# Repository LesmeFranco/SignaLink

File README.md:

<div align="center">

</div>

<div align="center">

# Tus gestos hablan, SignaLink traduce

</div>

## 🔗 Acceso a página web:

https://signalink2025.com

## 🗓️ Objetivo de Proyecto:

SignaLink tiene como objetivo principal traducir la lengua de señas para lograr la inclusión de personas sordas en el ámbito escolar.

## 🌎 Visión a futuro

Otro objetivo propuesto a largo plazo es seguir difundiendo esta idea en futuras generaciones para poder proveerles un mejor manejo en la vida cotidiana a este tipo de personas, permitiendole agilizar su vida social o simplemente la comunicación sin barerras con otras personas.

## 💭 ¿De dónde surgió la idea?

Esta idea surgió en una conversación con la bibliotecaria de nuestra escuela que nos dio a conocer cuan reservadas son estas personas en la sociedad y cuantos desafios deben afrontar a diario. A traves de todo esto planteamos posibles soluciones para facilitarle sus vidas inicialmente en las escuelas y asi empezo toda esta aventura.

## 🖐 Descripción del proyecto:

Nuestro proyecto esta principalmente equipado con sensores flex, giroscopos y acelerómetros que detectan los movimientos de los dedos.

Estos datos que arrojan los sensores son capturados por un ESP32 C3 Super Mini ubicado en la muñeca y enviados a un Computer module 4 (CM4) a traves de un sistema de mensajeria (MQTT) ubicado en el pecho/cintura. Esta CM4 integra una Inteligencia Artificial (IA) que se encarga de procesar estos datos recibidos para descubrir que gesto se intentó hacer. Una vez realizado este proceso se convertira mediante PIPER-TTS a formato audio reproducible por un parlante, permitiendo así que las personas que se comunican mediante la lengua de señas puedan expresar su mensaje de forma audible para que cualquier receptor lo comprenda.

En paralelo, un micrófono direccional se encargará de captar la voz de la persona que quiera comunicarse, esas palabras serán procesadas por la CM4 utilizando un modelo de reconocimiento de voz (Vosk -> Offline) y en forma de texto se mostrará finalmente a través de un LCD OLED (SSD1306)

<div align="center">

</div>

## 🛠️ Componentes a utilizar:

| Componentes                     | Links                                                                                                                                                                                                                                                                                                                                                                                                                                                                                                                                                                                                                                                                                                                                                                                            |
| ------------------------------- | ------------------------------------------------------------------------------------------------------------------------------------------------------------------------------------------------------------------------------------------------------------------------------------------------------------------------------------------------------------------------------------------------------------------------------------------------------------------------------------------------------------------------------------------------------------------------------------------------------------------------------------------------------------------------------------------------------------------------------------------------------------------------------------------------ |
| Raspberry Pi Compute Module 4   | [Raspberry Pi Compute Module 4 - ELEMON](https://www.elemon.com.ar/products/detail/code/AR681RA642)                                                                                                                                                                                                                                                                                                                                                                                                                                                                                                                                                                                                                                                                                              |
| ESP32-C3 Super Mini             | [ESP32-C3 Super Mini - Mercado Libre](https://articulo.mercadolibre.com.ar/MLA-1933180704-placa-desarrollo-esp32-c3-super-mini-wifi-bluetooth-sgk-_JM#polycard_client=search-nordic&position=18&search_layout=grid&type=item&tracking_id=a6179d80-9c2f-448f-931d-3f6b0744610e&wid=MLA1933180704&sid=search)                                                                                                                                                                                                                                                                                                                                                                                                                                                                                      |
| Sensores Flex                   | [Sensores Flex - Mercado Libre](https://articulo.mercadolibre.com.ar/MLA-621168012-flex-sensor-45-o-degrees-10-30-kohms-sensor-reflectivo-_JM#polycard_client=search-nordic&position=22&search_layout=stack&type=item&tracking_id=d09a116e-7fa9-4e61-b811-829b67d77fb1&wid=MLA621168012&sid=search)                                                                                                                                                                                                                                                                                                                                                                                                                                                                                              |
| Parlante                        | [ Mini Parlante- Mercado Libre](https://articulo.mercadolibre.com.ar/MLA-926965993-mini-parlante-mylar-50mm-8-ohms-05w-audio-arduino-nubbeo-_JM#polycard_client=search-nordic&position=8&search_layout=stack&type=item&tracking_id=5afdc171-789b-4858-9908-6e8644b818c2&wid=MLA926965993&sid=search)                                                                                                                                                                                                                                                                                                                                                                                                                                                                                             |
| Modulo Amplificador             | [ PAM8403 - Mercado Libre](https://www.mercadolibre.com.ar/mini-amplificador-digital-pam8403-audio-estereo-3w-nubbeo/up/MLAU237136317?pdp_filters=item_id:MLA872767061&matt_tool=93069454&matt_internal_campaign_id=345755545&matt_word=&matt_source=google&matt_campaign_id=22943760643&matt_ad_group_id=187007705242&matt_match_type=&matt_network=g&matt_device=c&matt_creative=774178775740&matt_keyword=&matt_ad_position=&matt_ad_type=pla&matt_merchant_id=5381779497&matt_product_id=MLA872767061&matt_product_partition_id=2424609165763&matt_target_id=pla-2424609165763&cq_src=google_ads&cq_cmp=22943760643&cq_net=g&cq_plt=gp&cq_med=pla&gad_source=1&gad_campaignid=22943760643&gclid=CjwKCAjwx-zHBhBhEiwA7Kjq67psJOORAgfFyvkqrNDuf2QOjtHhOilyAz1d6FZmyiqMh8wAA7Ma8xoCBCEQAvD_BwE) |
| Micrófono                       | [ Corbatero Carello C11 - Mercado Libre](https://www.mercadolibre.com.ar/microfono-inalambrico-corbatero-lavalier-carrello-c11-adaptador-usb-c-a-lightning-estuche-de-carga-antena-usb-c-1x-microfono-color-negro/p/MLA44118282)                                                                                                                                                                                                                                                                                                                                                                                                                                                                                                                                                                 |
| Baterias                        | [ Lipo 3.7V - Mercado Libre](https://articulo.mercadolibre.com.ar/MLA-823943306-bateria-litio-polimero-lipo-37v-1200mah-drones-helicopteros-_JM#polycard_client=search-nordic&position=11&search_layout=stack&type=item&tracking_id=00997a8f-a302-41cd-929e-7f9b96588b73&wid=MLA823943306&sid=search)                                                                                                                                                                                                                                                                                                                                                                                                                                                                                            |
| Sensor Giroscopo y Acelerometro | [MPU6050 - Mercado Libre](https://articulo.mercadolibre.com.ar/MLA-1464073846-acelerometro-giroscopo-mpu6050-6-ejes-gy-521-pic-arduino-_JM#polycard_client=search-nordic&position=4&search_layout=grid&type=item&tracking_id=1592b6fb-67c2-4128-a466-704776d0e915&wid=MLA1464073846&sid=search)                                                                                                                                                                                                                                                                                                                                                                                                                                                                                                  |
| Step Up 5V                      | [ MT3608 - Mercado Libre](https://articulo.mercadolibre.com.ar/MLA-1410408453-5-fuente-mt3608-step-up-buck-boost-elevador-dc-dc-28v-2a-_JM#polycard_client=search-nordic&backend_model=search-backend&position=20&search_layout=stack&type=item&tracking_id=d4915a5c-d355-42a4-b246-3798a3844913&wid=MLA1410408453&sid=search)                                                                                                                                                                                                                                                                                                                                                                                                                                                                   |
| LCD OLED                        | [LCD SSD1306 - Mercado Libre](https://articulo.mercadolibre.com.ar/MLA-1899526208-pantalla-display-oled-091-pulgadas-128x32-i2c-ssd1306-_JM)                                                                                                                                                                                                                                                                                                                                                                                                                                                                                                                                                                                                                                                     |

## 💻 Instalación y Uso

1. Clonar el repositorio:
   ```bash
   git clone https://github.com/impatrq/SignaLink
   ```
2. Entrar a la carpeta rpizero2W.
   ```bash
   cd SignaLink/rpizero2W
   ```
3. Darle permisos de ejecucion al script de instalación.
   ```bash
   chmod +x install.sh
   ```
4. Ejecutar el Script.
   ```bash
   ./install.sh
   ```
5. Comenzar su uso.

## 🧑🏽‍💻 Integrantes

| Integrantes           | Responsabilidades                     | Tareas Secundarias                 |
| --------------------- | ------------------------------------- | ---------------------------------- |
| Albornoz Thiago       | Gestión de Redes Sociales y Marketing | Desarrollo de Software             |
| Erbino Sebastián      | Diseño del Prototipo                  | Integración de hardware            |
| Franco Valentin       | Armado de Hardware                    | Instalación y conexión de hardware |
| Lesme Franco          | Armado de software                    | Diseño del prototipo               |
| Poggi Lorenzo         | Registro de Seguimiento               | Programación del sistema           |
| Sarniguette Valentino | Prueba electronica                    | Armado de circuitos                |

## 🤝 Colaboración:

Este es el comienzo de un prototipo realizado a base de nuestros conocimientos, si le gustaria formar parte de SignaLink, nos ayudaría su colaboración en:

- Perfeccionar el código.
- Mejorar la infraestructura tecnológica.
- Creación de manuales y realización de pruebas.
- Apoyo financiero para la investigación y el desarrollo.

## 📱 Contactanos:

 <div style="display: flex; justify-content: space-around;">

## 📱 Contactos personales

### 1. Albornoz Thiago

### 2. Erbino Sebastian

### 3. Franco Valentin

### 4. Lesme Franco

### 5. Poggi Lorenzo

</a>

### 6. Sarniguette Valentino

---

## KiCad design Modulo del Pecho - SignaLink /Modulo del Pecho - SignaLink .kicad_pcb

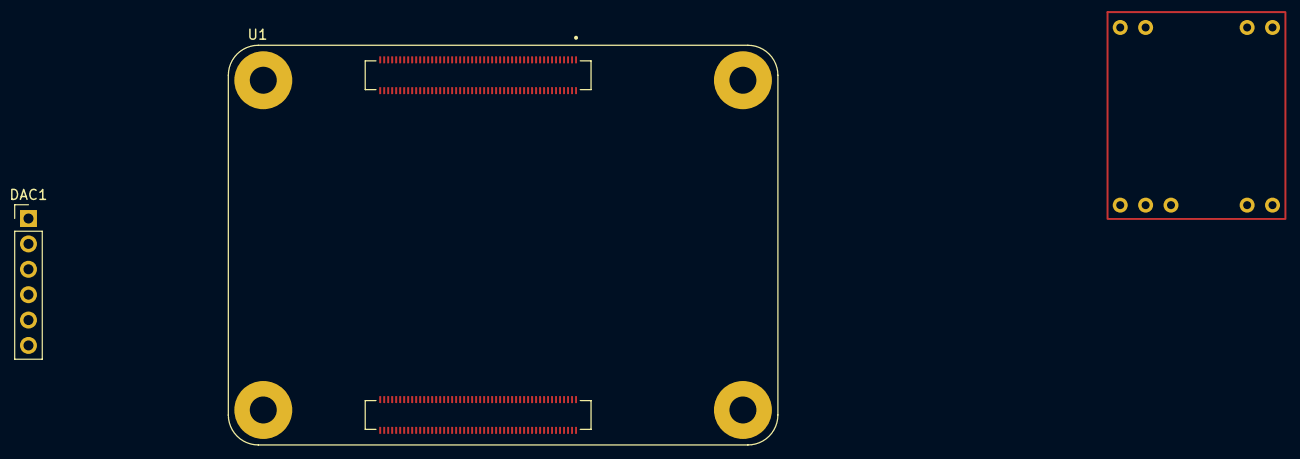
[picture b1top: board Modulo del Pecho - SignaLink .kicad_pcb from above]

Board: 2 copper layers, 3 parts (0 on the bottom side), 5 nets, no tracks yet.

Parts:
AMPL1: PAM8403
DAC1: PinHeader_1x06_P2.54mm_Vertical
U1: Raspberry; MODULE_SC0682

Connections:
unnamed: DAC1.1 (VIN), U1.77 (+5V(INPUT)), U1.79 (+5V(INPUT)), U1.81 (+5V(INPUT)), U1.83 (+5V(INPUT)), U1.85 (+5V(INPUT)), U1.87 (+5V(INPUT))
unnamed: U1.88 (CM4_1.8V(OUTPUT)), U1.90 (CM4_1.8V(OUTPUT))
unnamed: U1.84 (CM4_3.3V(OUTPUT)), U1.86 (CM4_3.3V(OUTPUT))
unnamed: U1.1 (GND), U1.2 (GND), U1.7 (GND), U1.8 (GND), U1.13 (GND), U1.14 (GND), U1.22 (GND), U1.23 (GND), U1.32 (GND), U1.33 (GND), U1.42 (GND), U1.43 (GND), U1.52 (GND), U1.53 (GND), U1.59 (GND), U1.60 (GND), U1.65 (GND), U1.66 (GND), U1.71 (GND), U1.74 (GND), U1.98 (GND), U1.107 (GND), U1.108 (GND), U1.113 (GND), U1.114 (GND), U1.119 (GND), U1.120 (GND), U1.125 (GND), U1.126 (GND), U1.131 (GND), U1.132 (GND), U1.137 (GND), U1.138 (GND), U1.144 (GND), U1.150 (GND), U1.155 (GND), U1.156 (GND), U1.161 (GND), U1.162 (GND), U1.167 (GND), U1.168 (GND), U1.173 (GND), U1.174 (GND), U1.179 (GND), U1.180 (GND), U1.185 (GND), U1.186 (GND), U1.191 (GND), U1.192 (GND), U1.197 (GND), U1.198 (GND)
unnamed: U1.SH1 (MOUNTING_PADS), U1.SH2 (MOUNTING_PADS), U1.SH3 (MOUNTING_PADS), U1.SH4 (MOUNTING_PADS)

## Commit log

2025-06-06 feat: agrego carpeta funcional de la confugracion BLE
2025-06-06 feat: agrego README
2025-06-06 chore: modificaciones en el codigo
2025-06-09 feat: agrego archiv .gitignore
2025-06-09 prueba flex
2025-06-10 chore: eliminación de carpetas
2025-06-10 chore: eliinacion de gitigonre
2025-06-10 feat: nuevo funcionamiento de la conexión BLE
2025-06-11 feat: borro elementos innecesarios
2025-06-11 flex
2025-06-11 fix: corregir errores en la funcionalidad BLE
2025-06-12 feat: agregar funcional BLE para sensores flex
2025-06-12 nueva rama BLE
2025-06-12 feat.BLE
2025-06-13 feat: actualizo archivos
2025-06-13 Directorio de raspberry Pi Zero 2W con Script de instalacion de dependencias necesarias
2025-06-19 Update README.md
    cambio en el LCD
2025-06-19 feat: Actualizo nuevas funciones, imagenes, y otras cosas para la página web
2025-06-19 chore: muevo de lugar los archivos
2025-06-19 chore: subo archivos borrados accidentalmente
2025-06-19 fix: corrección del readme
2025-06-25 UART
2025-07-10 Modificaciones y eliminacion de requerimientos innecesarios
2025-07-12 Modificaciones del requirements.txt
2025-07-12 Primera prueba del microfono y primero reconocimiento de voz realizado
2025-08-04 feat: actualizo imagenes del readme
2025-08-04 fix: imagenes
2025-08-20 muevo la v1.1 de la pagina a su carpeta correspondiente
2025-08-25 nuevos parametros de sensores flex
2025-08-26 chore: elimino carpeta que esta de mas
2025-08-26 feat: agregar funcion del oled lcd
2025-08-26 Revert "feat: agregar funcion del oled lcd"
2025-08-27 Muevo carpetas
2025-08-27 cambio dos valores de parametros de flex
2025-08-27 fix: modificaciones en gatt_client
2025-08-27 chore: elimino carpeta vieja de gatt_client
2025-08-27 feat: ahora si agrego la carpeta que esta bien
2025-09-02 fix: elimino vieja carpeta de pagina web
2025-09-02 feat: Acomodo todo en carpetas y subo version final de webpage
2025-09-02 chore: elimino licencia
2025-09-02 feat: Datasheets usados
2025-09-02 feat: Agrego datasheet de flex
2025-09-03 feat: nueva funcion ble
2025-09-03 agrego imagen
2025-09-03 cambio de recepcion en cliente de notificacion
2025-09-03 cambios de informacion enviada al cliente
2025-09-03 inicializando angulos
2025-09-03 chore: sdkconfig
2025-09-03 chore: .vscode
2025-09-03 docs: Muevo todo a carpetas correspondientes
2025-09-03 cambios en notificacion de client
2025-09-03 edit para que arranquen los flex desde la misma resistencia
2025-09-03 creo carpetas de experimentación e imagenes
2025-09-03 muevo carpeta del MAX9814 y fixeo readme
2025-09-03 agrego carpeta de img
2025-09-03 creo carpeta de imagenes y subo logo al readme
2025-09-03 fix en proceso
2025-09-03 Elimino carpeta rpizero2w para trabajar en otra rama
2025-09-09 fix: codigo corriendo
2025-09-16 docs: datasheet del PCM5102 agregado
2025-09-18 docs: datasheet de referencias
2025-09-19 preparo para PR
2025-09-19 docs: muevo carpetas a su respectivo lugar
2025-09-19 docs: creo carpeta principal de prototipo 3D
2025-09-19 docs: agrego anteproyecto
2025-09-26 clean: limpieza de archivos en la rama de placaas
2025-09-26 feat: agrego carpeta del modulo del pecho
    En esta carpeta se encuentra el esquematico y el pcb para la placa que vamos a hacer para el modulo del pecho
2025-09-26 feat: agrego carpeta que contiene las bibliotecas
    Esta carpeta contiene tanto los esquemas de los sensores y sus huellas
2025-09-26 feat: adjunto imagenes de las placas de la muñeca
2025-09-26 fix: modificaciones en el README
2025-09-26 refactor: arreglo tamaño de imagenes
2025-09-26 Primer opción para soporte de sensores flex
2025-09-26 Separaciones de las falanges
    Con el fin de que el soporte sea funcional, tuve que modificar el archivo en SolidWorks para su impresión
2025-09-26 Segunda opción para soporte de los sensores flex
    Pensando en la experiencia del usuario y el posible uso diario del dispositivo, decidimos cambiar el diseño por uno mucho más ergonómico y compacto
2025-09-26 Reescala del diseño del soporte
    El tamaño del diseño era incorrecto y no permitía el uso para los usuarios
2025-09-26 Prototipo 1.0 para modulo mano
    Una caja que puede albergar nuestro diseño minimalista
2025-09-26 Mejoramos el modulo muñeca
    Se le agregó nuestro nombre a la tapa del modulo y se mejoró el sistema de deslizamiento de la tapa
2025-09-30 feat: agrego carpeta para el entrenamiento de la ia
2025-10-01 fix: correcciones en el README.md
2025-10-07 fix: rm zip
2025-10-07 Correccion de README y fotos
    Paso a enviar las capturas y archivos de el diseño hecho en KiCad del modulo de muñeca finalizado de manera correcta. Tambien se subio las fotos y se hicieron correcciones importantes en el README
2025-10-07 Creo rama y subo carpeta técnica
2025-10-10 feat: agrego carpeta funcional con el codigo para el entrenamiento de la ia
2025-10-10 feat: agrego archivos del modulo del pecho
2025-10-14 docs: subo version final de carpeta tecnica
2025-10-20 Subo carpeta de campo
2025-10-20 fix: modificacion de codigo de Inteligencia Artificial
    dejo el codigo funcional de TensorFlow junto a los archivos.tflite y archivos.pkl que usara la Raspberry al momento de hacer las predicciones. Tambien dejo la carpeta de las señas grabadas
2025-10-20 Revert "Merge pull request #11 from impatrq/feat/inteligencia-artificial"
    This reverts commit 0c01355a68b9af7e4bbc427d745f599da2ae97a5, reversing
    changes made to de9e4948159d5aa00238311e8ab8d4d5ebc15e46.
2025-10-20 fix:subo carpeta tecnica arreglada
2025-10-20 cambios
2025-10-20 feat: agrego carpeta de Inteligencia Artificial
2025-10-20 fix: modifico rutas de imagenes del pecho
2025-10-20 Sumando el readme la placa derecha
2025-10-20 renombro carpeta
2025-10-20 Revert "Merge pull request #12 from impatrq/docs/documentación"
    This reverts commit 0fd6f23288b287a432f4e167715ffb0d6992e729, reversing
    changes made to 4a4a6f65963e39984e1c6e33d6f23d696b10295b.
2025-10-24 fix: intentando hacer pull requests
2025-10-24 fix: main traido a rama para luego hacer PR
2025-10-24 docs: README actualizado

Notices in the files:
README.md:
License: MIT
